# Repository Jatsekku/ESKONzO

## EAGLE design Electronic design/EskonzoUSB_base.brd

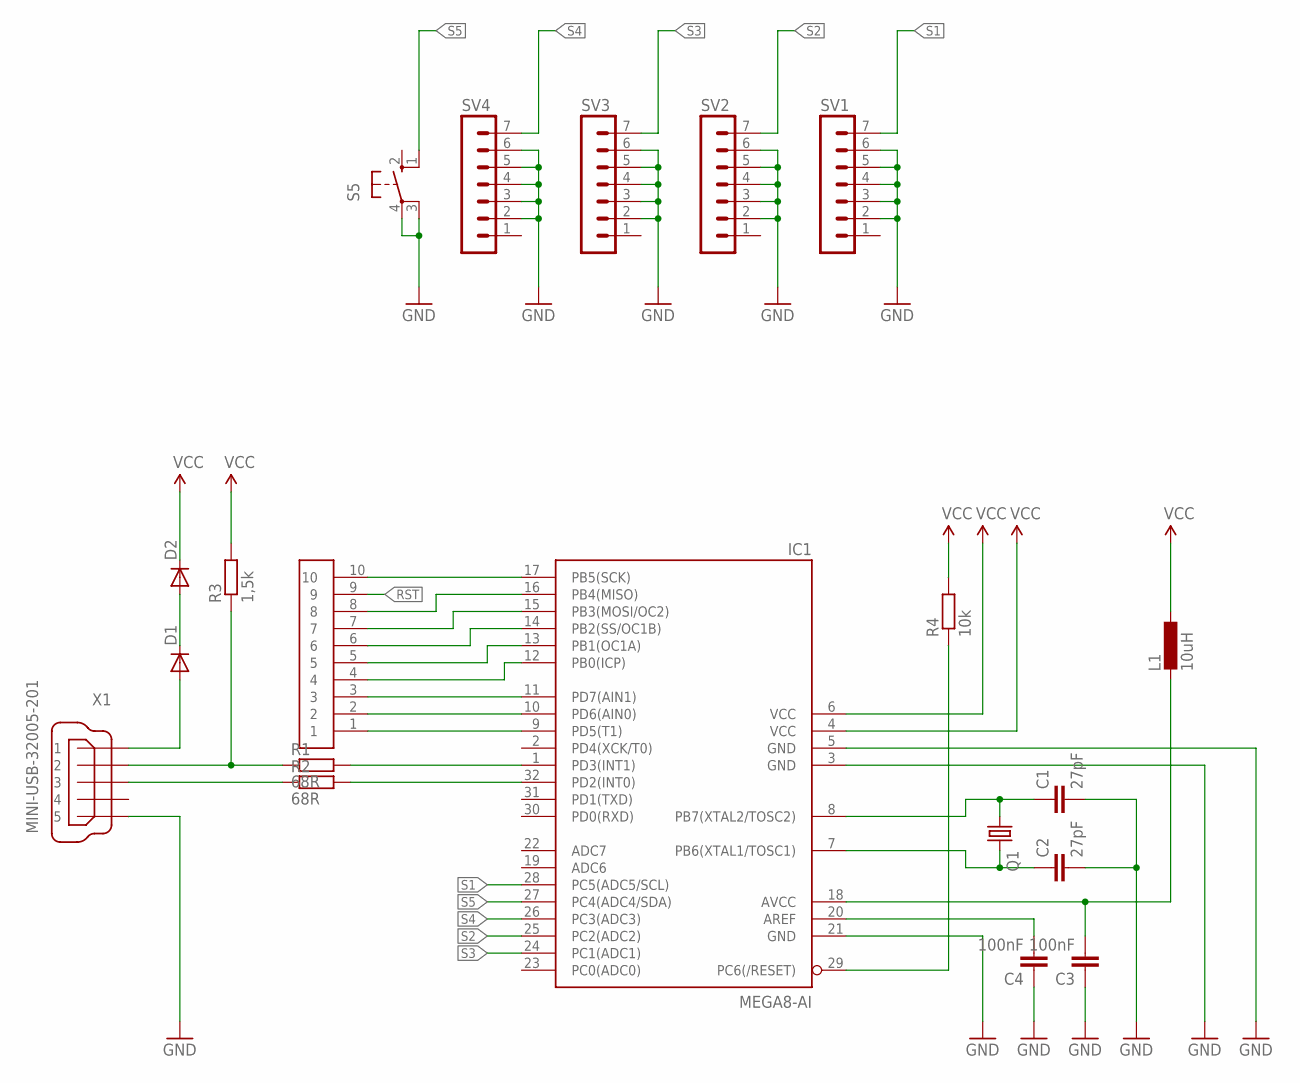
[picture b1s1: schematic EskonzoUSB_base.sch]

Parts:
C1, C2: 27pF; C0805
C3, C4: 100nF; C0805
D1, D2: DIODE-MELF-MLL41; MELF-MLL41
IC1: MEGA8-AI; TQFP32-08
L1: 10uH; L1812
Q1: CRYSTALHC49UP; HC49UP
R1, R2: 68R; R0805
R3: 1,5k; R0805
R4: 10k; R0805
S5: 40-XX_SMD; B3F-40XX_SMD
SV1, SV2, SV3, SV4: MA07-1_SMD
U$1: PINY_1X9_1.27MM_SMT
X1: MINI-USB-32005-201; 32005-201

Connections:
GND: C1.2, C2.2, C3.1, C4.1, IC1.3 (GND), IC1.5 (GND), IC1.21 (GND), S5.3 (P1), S5.4, SV1.2, SV1.3, SV1.4, SV1.5, SV1.6, SV2.2, SV2.3, SV2.4, SV2.5, SV2.6, SV3.2, SV3.3, SV3.4, SV3.5, SV3.6, SV4.2, SV4.3, SV4.4, SV4.5, SV4.6, X1.5
unnamed: R1.1, R3.1, X1.2
unnamed: R2.1, X1.3
unnamed: IC1.1 (PD3(INT1)), R1.2
unnamed: IC1.32 (PD2(INT0)), R2.2
unnamed: D1.A, X1.1
unnamed: D1.C, D2.A
unnamed: C1.1, IC1.8 (PB7(XTAL2/TOSC2)), Q1.1
unnamed: C2.1, IC1.7 (PB6(XTAL1/TOSC1)), Q1.2
unnamed: C3.2, IC1.18 (AVCC), L1.2
unnamed: IC1.17 (PB5(SCK)), U$1.10
unnamed: C4.2, IC1.20 (AREF)
unnamed: IC1.15 (PB3(MOSI/OC2)), U$1.7
unnamed: IC1.16 (PB4(MISO)), U$1.8
unnamed: IC1.14 (PB2(SS/OC1B)), U$1.6
unnamed: IC1.13 (PB1(OC1A)), U$1.5
unnamed: IC1.12 (PB0(ICP)), U$1.4
unnamed: IC1.11 (PD7(AIN1)), U$1.3
unnamed: IC1.10 (PD6(AIN0)), U$1.2
unnamed: IC1.9 (PD5(T1)), U$1.1
RST: IC1.29 (PC6(/RESET)), R4.1, U$1.9
S1: IC1.28 (PC5(ADC5/SCL)), SV1.7
S2: IC1.25 (PC2(ADC2)), SV2.7
S3: IC1.24 (PC1(ADC1)), SV3.7
S4: IC1.26 (PC3(ADC3)), SV4.7
S5: IC1.27 (PC4(ADC4/SDA)), S5.1 (S1)
VCC: D2.C, IC1.4 (VCC), IC1.6 (VCC), L1.1, R3.2, R4.2

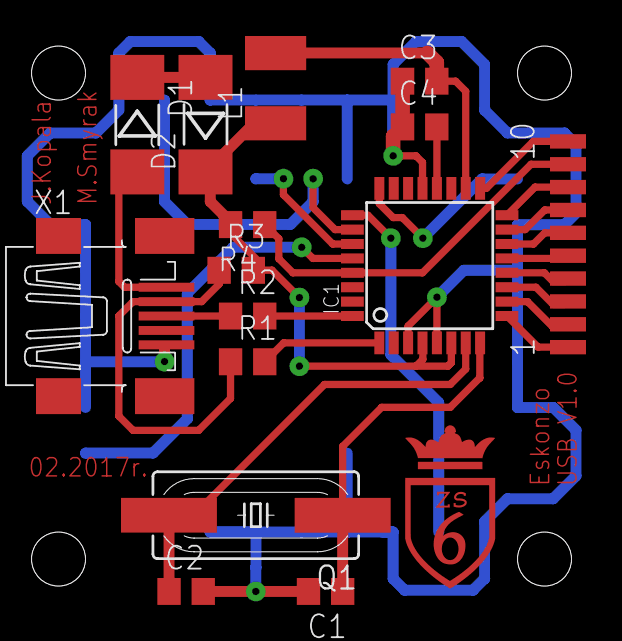
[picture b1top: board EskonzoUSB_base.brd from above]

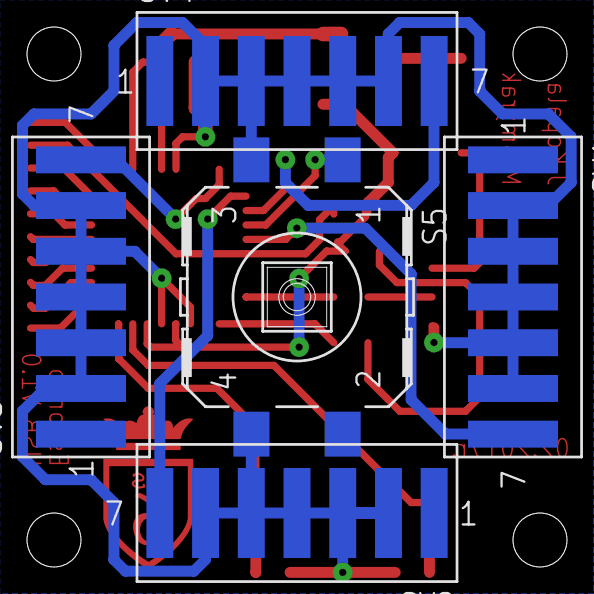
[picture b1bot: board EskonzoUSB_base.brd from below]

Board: 2 copper layers, 20 parts (5 on the bottom side), 27 nets.

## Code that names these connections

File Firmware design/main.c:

#include <avr/io.h>			//Biblioteka I/O.
#include <avr/interrupt.h>  //Biblioteka obs³ugi przerwañ.
#include <avr/wdt.h>		//Biblioteka obs³ugi watchdog'a.
#include <util/delay.h>		//Biblioteka opónieñ czasowych.

#include "usbdrv/usbdrv.h"	//Biblioteka implementacji programowej interfejsu USB.

//Makrodefinicje przycisków.
#define S_DOWN		PC5
#define S_UP		PC1
#define S_LEFT		PC3
#define S_RIGHT		PC2
#define S_LPM		PC4

#define LOW_SPEED				5		//Mniejsza prêdkoæ kursora.
#define HIGH_SPEED				15		//Wiêksza prêdkoæ kursora.
#define STOP 					0		//Zatrzymanie kursora.
//Iloæ inkrementacji po której nastêpuje zwiêkszenie prêdkoci kursora.
#define LOW2HIGH_LOOP_FACTOR	200000

//Deskryptor urz¹dzenia
const PROGMEM char usbHidReportDescriptor[52] = { /* USB report descriptor, size must match usbconfig.h */
    0x05, 0x01,                    // USAGE_PAGE (Generic Desktop)
    0x09, 0x02,                    // USAGE (Mouse)
    0xa1, 0x01,                    // COLLECTION (Application)
    0x09, 0x01,                    //   USAGE (Pointer)
    0xA1, 0x00,                    //   COLLECTION (Physical)
    0x05, 0x09,                    //     USAGE_PAGE (Button)
    0x19, 0x01,                    //     USAGE_MINIMUM
    0x29, 0x03,                    //     USAGE_MAXIMUM
    0x15, 0x00,                    //     LOGICAL_MINIMUM (0)
    0x25, 0x01,                    //     LOGICAL_MAXIMUM (1)
    0x95, 0x03,                    //     REPORT_COUNT (3)
    0x75, 0x01,                    //     REPORT_SIZE (1)
    0x81, 0x02,                    //     INPUT (Data,Var,Abs)
    0x95, 0x01,                    //     REPORT_COUNT (1)
    0x75, 0x05,                    //     REPORT_SIZE (5)
    0x81, 0x03,                    //     INPUT (Const,Var,Abs)
    0x05, 0x01,                    //     USAGE_PAGE (Generic Desktop)
    0x09, 0x30,                    //     USAGE (X)
    0x09, 0x31,                    //     USAGE (Y)
    0x09, 0x38,                    //     USAGE (Wheel)
    0x15, 0x81,                    //     LOGICAL_MINIMUM (-127)
    0x25, 0x7F,                    //     LOGICAL_MAXIMUM (127)
    0x75, 0x08,                    //     REPORT_SIZE (8)
    0x95, 0x03,                    //     REPORT_COUNT (3)
    0x81, 0x06,                    //     INPUT (Data,Var,Rel)
    0xC0,                          //   END_COLLECTION
    0xC0,                          // END COLLECTION
};

//Deklaracja struktury - g³ówne cechy kursora.
typedef struct{
    uint8_t   button;
    int8_t    dx;
    int8_t    dy;
    char      dWheel;
} report_t;

static report_t Eskonzo;	//Utworzenie struktury

//Inicjalizacja
static uchar    idleRate;
usbMsgLen_t usbFunctionSetup(uchar data[8]) {
    usbRequest_t *rq = (void *)data;
    if((rq->bmRequestType & USBRQ_TYPE_MASK) == USBRQ_TYPE_CLASS) {
        if(rq->bRequest == USBRQ_HID_GET_REPORT) {
            usbMsgPtr = (void *)&Eskonzo;
            return sizeof(Eskonzo);
        } else if(rq->bRequest == USBRQ_HID_GET_IDLE) {
            usbMsgPtr = &idleRate;
            return 1;
        } else if(rq->bRequest == USBRQ_HID_SET_IDLE) {
            idleRate = rq->wValue.bytes[1];
        }
    }
    return 0;
}

//Funkcja g³ówna programu.
int main()
{
	DDRC = 0x00;				//Ustawienie ca³ego portu C jako wejcia.
	PORTC = 0xFF;				//Ustawienie podci¹gniêæ do VCC na ca³ym porcie C.

	uint32_t Eskonzo_AX = 0; 	//Utworzenie zmiennej inkrementacyjnej dla osi X
	uint32_t Eskonzo_AY = 0; 	//Utworzenie zmiennej inkrementacyjnej dla osi Y

    wdt_enable(WDTO_1S); 		//Uruchomienie watchdog'a z 1s okresem.
    usbInit();					//Wywo³anie inicjalizacji USB.
    usbDeviceDisconnect();  	//Zakoñczenie po³¹czenia

    //Oczekiwanie 500ms
    for(uint8_t i = 0; i<250; i++) 	//Powtórzenie operacji 250 razy
    {
        wdt_reset();	//Reset watchdoga
        _delay_ms(2);	//Oczekiwanie 2ms
    }

    usbDeviceConnect();	//Nawi¹zanie nowego po³¹czenia.
    sei(); 				//Uruchomienie przerwañ globalnych

    //Pêtla g³ówna programu
    while(1)
    {
        wdt_reset();	//Reset watchdoga
        usbPoll();		//Cyklicznie wywo³ywania funkcja sprawdzania stanu interfejsu USB (pooling).

        /*Szereg warunków determinuj¹cych dzia³anie Eskonzo - w nieskoñczonej petli sprawdzane s¹ kolejno
          poszczególne piny portu C do którego do³¹czone s¹ mikrostyki. W wypadku przytrzymywania dwigni
          urz¹dzenia w danym kierunku, nastêpujê inkrementacja zmiennej (Eskonzo_AY/AX), co stanowi podstawê
          do okrelania jak d³ugo ów przytrzymywanie trwa³o.*/

        if(!(PINC & (1<<S_UP)))
        {
        	Eskonzo.dy = LOW_SPEED;
        	Eskonzo_AY++;
        	if(Eskonzo_AY>LOW2HIGH_LOOP_FACTOR) Eskonzo_AY= LOW2HIGH_LOOP_FACTOR;
        	if(Eskonzo_AY>=LOW2HIGH_LOOP_FACTOR) Eskonzo.dy = HIGH_SPEED;
        }
        else if(!(PINC & (1<<S_DOWN)))
        {
        	Eskonzo.dy = -LOW_SPEED;
        	Eskonzo_AY++;
        	if(Eskonzo_AY>LOW2HIGH_LOOP_FACTOR) Eskonzo_AY= LOW2HIGH_LOOP_FACTOR;
        	if(Eskonzo_AY>=LOW2HIGH_LOOP_FACTOR) Eskonzo.dy = -HIGH_SPEED;
        }
        else
        {
        	Eskonzo.dy = 0;
        	Eskonzo_AY = 0;
        }

        if(!(PINC & (1<<S_LEFT)))
        {
        	Eskonzo.dx = -LOW_SPEED;
        	Eskonzo_AX++;
        	if(Eskonzo_AX>LOW2HIGH_LOOP_FACTOR) Eskonzo_AX= LOW2HIGH_LOOP_FACTOR;
        	if(Eskonzo_AX>=LOW2HIGH_LOOP_FACTOR) Eskonzo.dx = -HIGH_SPEED;
        }
        else if(!(PINC & (1<<S_RIGHT)))
        {
        	Eskonzo.dx = LOW_SPEED;
        	Eskonzo_AX++;
        	if(Eskonzo_AX>LOW2HIGH_LOOP_FACTOR) Eskonzo_AX= LOW2HIGH_LOOP_FACTOR;
        	if(Eskonzo_AX>=LOW2HIGH_LOOP_FACTOR) Eskonzo.dx = HIGH_SPEED;
        }
        else
        {
        	Eskonzo.dx = 0;
        	Eskonzo_AX = 0;
        }

        if(!(PINC & (1<<S_LPM))) Eskonzo.button = 1;
        else					 Eskonzo.button = 0;

        /*Sprawdzenie czy nast¹pi³o zapytanie od strony hosta, jeli tak to nastêpuje
          do³¹czenie zaktualizowanej struktury do przesy³anej ramki danych.*/

        if(usbInterruptIsReady()) usbSetInterrupt((void *)&Eskonzo, sizeof(Eskonzo));

    }
    return 0;
}

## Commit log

2020-02-26 Original ESKONzO files

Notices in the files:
parts and their libraries:
SparkFun-Aesthetics: Licensing: Creative Commons ShareAlike 4.0 International - https://creativecommons.org/licenses/by-sa/4.0
